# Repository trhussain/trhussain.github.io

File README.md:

npm run deploy 
- pushes to gh-pages dir

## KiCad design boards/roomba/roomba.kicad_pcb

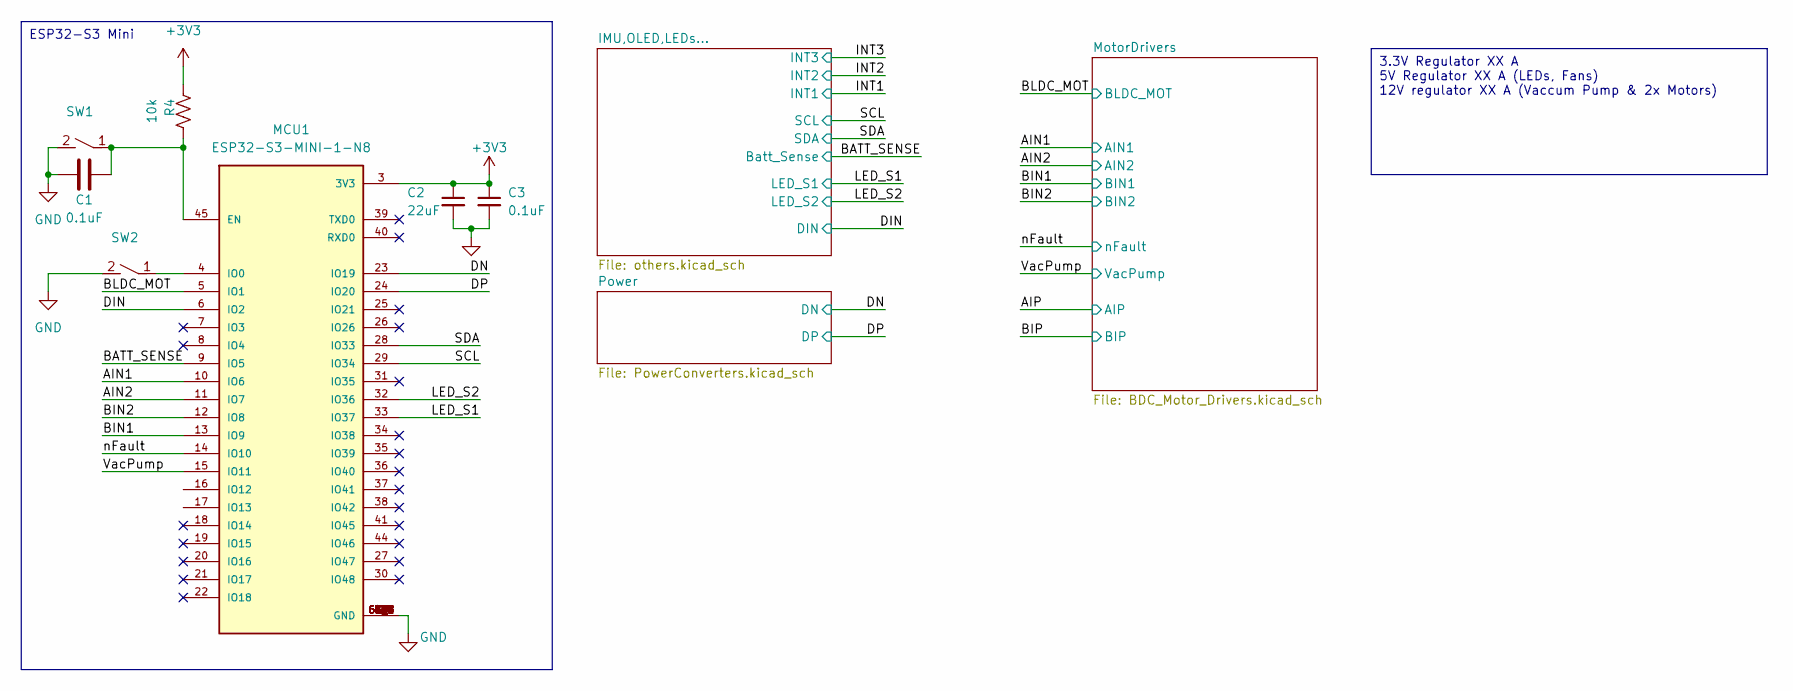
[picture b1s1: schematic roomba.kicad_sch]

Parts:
C1, C3: 0.1uF; C_0603_1608Metric
C2: 22uF; C_0603_1608Metric
MCU1: ESP32-S3-MINI-1-N8; XCVR_ESP32-S3-MINI-1-N8; PARTREV v0.6
R4: 10k; R_0603_1608Metric
SW1, SW2: rockerSwitch-434133025816

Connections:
+3V3: C2.1, C3.1, MCU1.3 (3V3), R4.2; also elsewhere on the board
/AIN1: MCU1.10 (IO6); also elsewhere on the board
/AIN2: MCU1.11 (IO7); also elsewhere on the board
/BATT_SENSE: MCU1.9 (IO5); also elsewhere on the board
/BIN1: MCU1.13 (IO9); also elsewhere on the board
/BIN2: MCU1.12 (IO8); also elsewhere on the board
/BLDC_MOT: MCU1.5 (IO1); also elsewhere on the board
/DIN: MCU1.6 (IO2); also elsewhere on the board
/DN: MCU1.23 (IO19); also elsewhere on the board
/DP: MCU1.24 (IO20); also elsewhere on the board
/LED_S1: MCU1.33 (IO37); also elsewhere on the board
/LED_S2: MCU1.32 (IO36); also elsewhere on the board
/SCL: MCU1.29 (IO34); also elsewhere on the board
/SDA: MCU1.28 (IO33); also elsewhere on the board
/VacPump: MCU1.15 (IO11); also elsewhere on the board
/nFault: MCU1.14 (IO10); also elsewhere on the board
GND: C1.1, C2.2, C3.2, MCU1.1 (GND), MCU1.2 (GND), MCU1.42 (GND), MCU1.43 (GND), MCU1.46 (GND), MCU1.47 (GND), MCU1.48 (GND), MCU1.49 (GND), MCU1.50 (GND), MCU1.51 (GND), MCU1.52 (GND), MCU1.53 (GND), MCU1.54 (GND), MCU1.55 (GND), MCU1.56 (GND), MCU1.57 (GND), MCU1.58 (GND), MCU1.59 (GND), MCU1.60 (GND), MCU1.61 (GND), MCU1.61_1 (GND), MCU1.61_2 (GND), MCU1.61_3 (GND), MCU1.61_4 (GND), MCU1.61_5 (GND), MCU1.61_6 (GND), MCU1.61_7 (GND), MCU1.61_8 (GND), MCU1.62 (GND), MCU1.63 (GND), MCU1.64 (GND), MCU1.65 (GND), SW1.2, SW2.2; also elsewhere on the board
unnamed: C1.2, MCU1.45 (EN), R4.1, SW1.1
unnamed: MCU1.4 (IO0), SW2.1

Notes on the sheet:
3.3V Regulator XX A 5V Regulator XX A (LEDs, Fans) 12V regulator XX A (Vaccum Pump & 2x Motors)
ESP32-S3 Mini

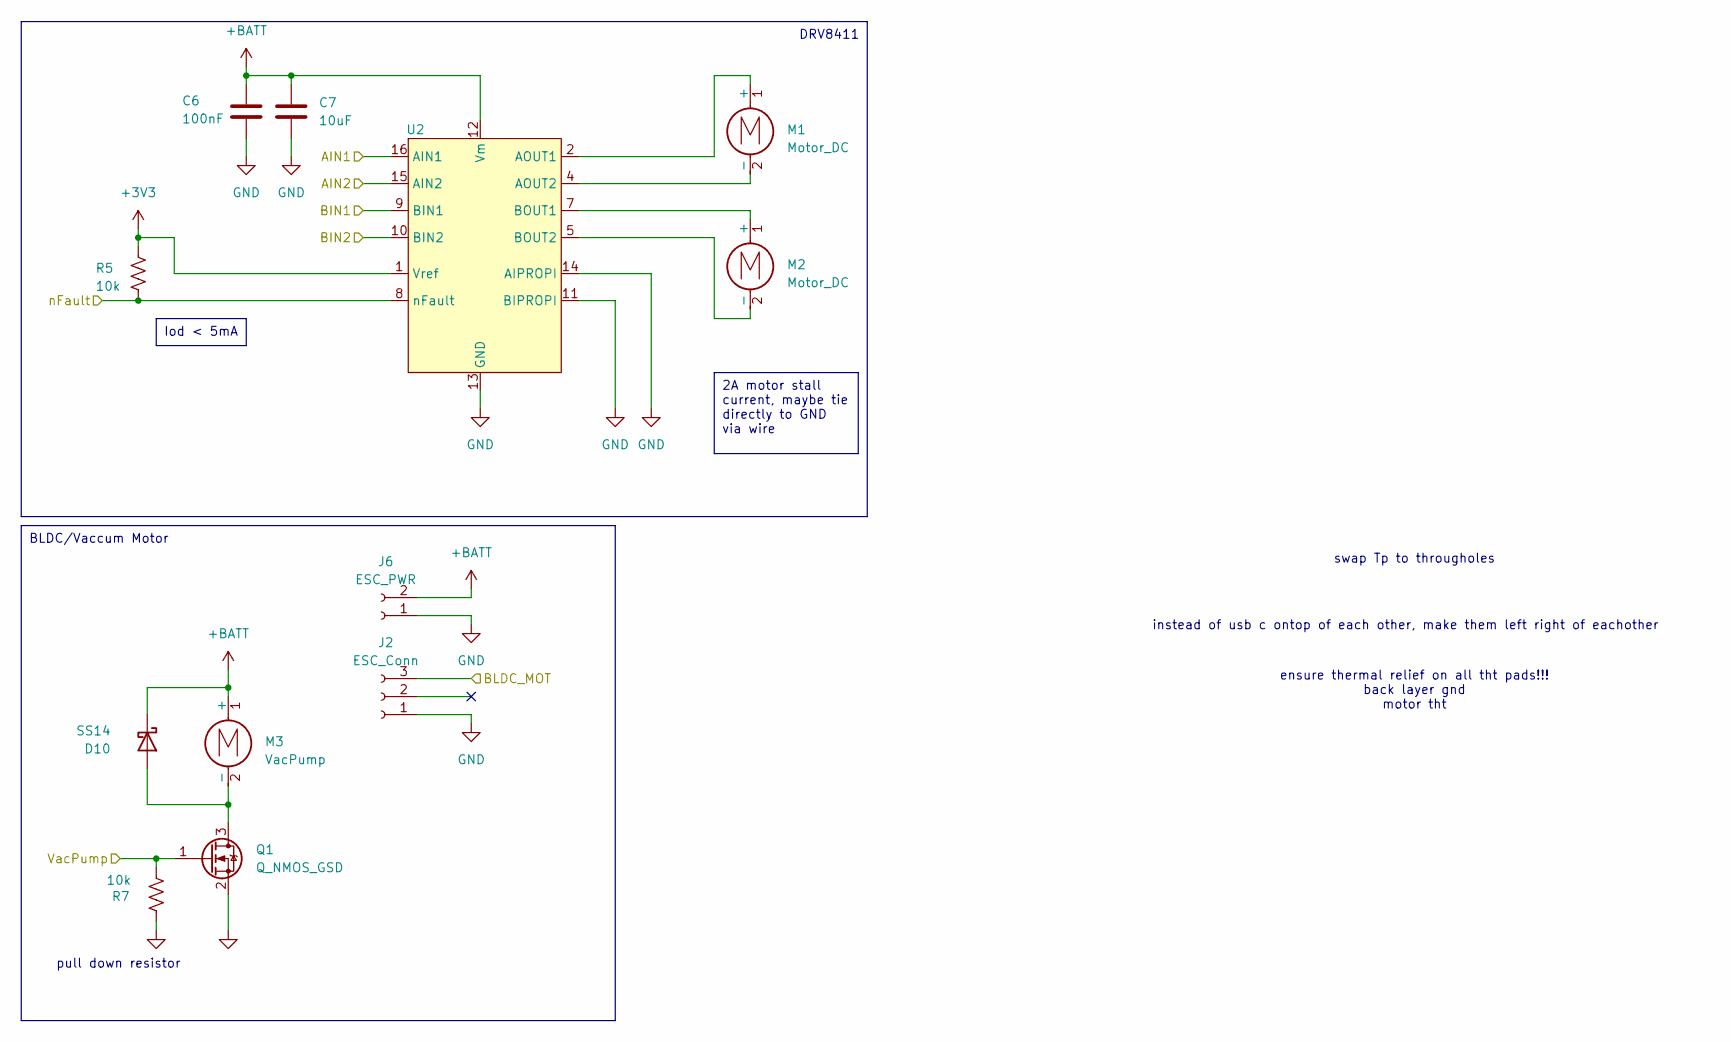
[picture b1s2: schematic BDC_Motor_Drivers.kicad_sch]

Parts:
C6: 100nF; C_0603_1608Metric_Pad1.08x0.95mm_HandSolder
C7: 10uF; C_0603_1608Metric_Pad1.08x0.95mm_HandSolder
D10: SS14; D_SMA
J2: ESC_Conn; PinHeader_1x03_P2.54mm_Horizontal
J6: ESC_PWR; PinSocket_1x02_P2.54mm_Vertical
M1, M2: Motor_DC; PinHeader_1x02_P2.54mm_Vertical
M3: VacPump; PinHeader_1x02_P2.54mm_Vertical
Q1: Q_NMOS_GSD; SOT-23-3
R5, R7: 10k; R_0603_1608Metric
U2: DRV8411A; TSSOP-DRV8411A

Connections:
+3V3: R5.1, U2.1 (Vref); also elsewhere on the board
+BATT: C6.1, C7.1, D10.1 (K), J6.2, M3.1 (+), U2.12 (Vm); also elsewhere on the board
/AIN1: U2.16 (AIN1); also elsewhere on the board
/AIN2: U2.15 (AIN2); also elsewhere on the board
/BIN1: U2.9 (BIN1); also elsewhere on the board
/BIN2: U2.10 (BIN2); also elsewhere on the board
/BLDC_MOT: J2.3; also elsewhere on the board
/VacPump: Q1.1 (G), R7.2; also elsewhere on the board
/nFault: R5.2, U2.8 (nFault); also elsewhere on the board
GND: C6.2, C7.2, J2.1, J6.1, Q1.2 (S), R7.1, U2.3 (PGNDA), U2.6 (PGNDB), U2.11 (BIPROPI), U2.13 (GND), U2.14 (AIPROPI), U2.19 (BODYGND); also elsewhere on the board
unnamed: D10.2 (A), M3.2 (-), Q1.3 (D)
unnamed: M1.1 (+), U2.2 (AOUT1)
unnamed: M1.2 (-), U2.4 (AOUT2)
unnamed: M2.1 (+), U2.7 (BOUT1)
unnamed: M2.2 (-), U2.5 (BOUT2)

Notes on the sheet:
Iod < 5mA
2A motor stall current, maybe tie directly to GND via wire
DRV8411
BLDC/Vaccum Motor
instead of usb c ontop of each other, make them left right of eachother
pull down resistor
ensure thermal relief on all tht pads!!! back layer gnd motor tht
swap Tp to througholes

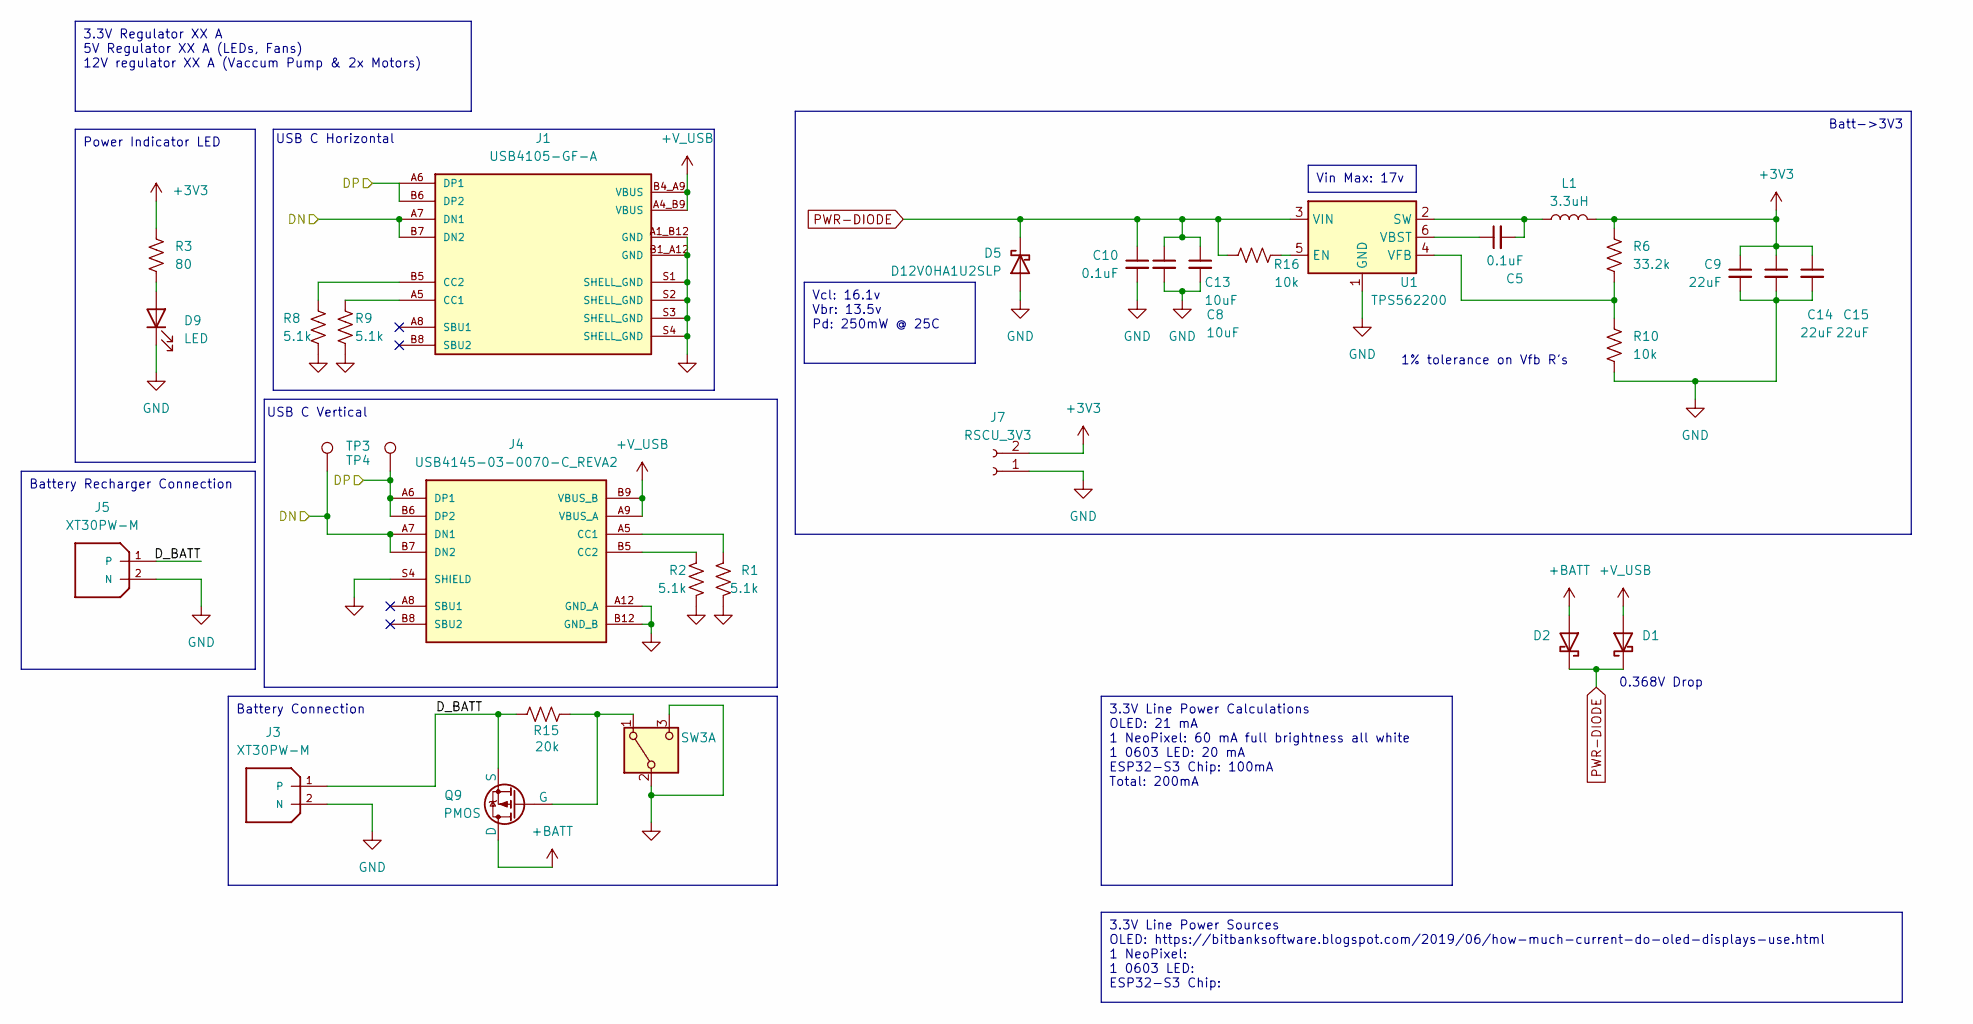
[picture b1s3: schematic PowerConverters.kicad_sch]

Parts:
C5, C10: 0.1uF; C_0603_1608Metric
C8, C13: 10uF; C_0603_1608Metric
C9, C14, C15: 22uF; C_0603_1608Metric
D1, D2: SS38; D_SOD-128
D5: D12V0HA1U2SLP; D_SOD-882
D9: LED; LED_0603_1608Metric
J1: USB4105-GF-A; GCT_USB4105-GF-A; PARTREV A3
J3: XT30PW-M; AMASS_XT30PW-M; PARTREV 1.2
J4: USB4145-03-0070-C_REVA2; GCT_USB4145-03-0070-C_REVA2; PARTREV A2
J5: XT30PW-M; AMASS_XT30U-F_1x02_P5.0mm_Vertical; PARTREV 1.2
J7: RSCU_3V3; PinSocket_1x02_P2.54mm_Vertical
L1: 3.3uH; L_TDK_VLS6045EX_VLS6045AF
Q9: PMOS; PowerPAK_SO-8_Single
R1, R2, R8, R9: 5.1k; R_0603_1608Metric
R3: 80; R_0603_1608Metric
R6: 33.2k; R_0603_1608Metric
R10, R16: 10k; R_0603_1608Metric
R15: 20k; R_0603_1608Metric
SW3: SW_Nidec_CAS-120A1; SW_JS102011JAQN
TP3, TP4: TestPoint; TestPoint_Pad_1.0x1.0mm
U1: TPS562200; SOT-23-6

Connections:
+3V3: C9.1, C14.1, C15.1, J7.2, L1.2, R3.1, R6.1; also elsewhere on the board
+BATT: D2.2 (A), Q9.5 (D); also elsewhere on the board
+V_USB: D1.2 (A), J1.A4_B9 (VBUS), J1.B4_A9 (VBUS), J4.A4 (VBUS_A), J4.A9 (VBUS_A), J4.B4 (VBUS_B), J4.B9 (VBUS_B)
/DN: J1.A7 (DN1), J1.B7 (DN2), J4.A7 (DN1), J4.B7 (DN2), TP3.1; also elsewhere on the board
/DP: J1.A6 (DP1), J1.B6 (DP2), J4.A6 (DP1), J4.B6 (DP2), TP4.1; also elsewhere on the board
/Power/D_BATT: J3.1, J5.1, Q9.1 (S), Q9.2 (S), Q9.3 (S), R15.2
GND: C8.2, C9.2, C10.2, C13.2, C14.2, C15.2, D5.2 (A), D9.1 (K), J1.A1_B12 (GND), J1.B1_A12 (GND), J1.S1 (SHELL_GND), J1.S2 (SHELL_GND), J1.S3 (SHELL_GND), J1.S4 (SHELL_GND), J3.2 (N), J4.A1 (GND_A), J4.A12 (GND_A), J4.B1 (GND_B), J4.B12 (GND_B), J4.S1 (SHIELD), J4.S2 (SHIELD), J4.S3 (SHIELD), J4.S4 (SHIELD), J5.2 (N), J7.1, R1.2, R2.2, R8.2, R9.2, R10.2, SW3.2 (B), SW3.3 (C), U1.1 (GND); also elsewhere on the board
unnamed: D9.2 (A), R3.2
unnamed: J1.A5 (CC1), R9.1
unnamed: J1.B5 (CC2), R8.1
unnamed: J4.A5 (CC1), R1.1
unnamed: J4.B5 (CC2), R2.1
unnamed: Q9.4 (G), R15.1, SW3.1 (A)
unnamed: R16.2, U1.5 (EN)
unnamed: C5.2, L1.1, U1.2 (SW)
unnamed: C5.1, U1.6 (VBST)
unnamed: R6.2, R10.1, U1.4 (VFB)
PWR-DIODE: C8.1, C10.1, C13.1, D1.1 (K), D2.1 (K), D5.1 (K), R16.1, U1.3 (VIN)

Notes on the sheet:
Vcl: 16.1v Vbr: 13.5v Pd: 250mW @ 25C
3.3V Line Power Calculations OLED: 21 mA 1 NeoPixel: 60 mA full brightness all white 1 0603 LED: 20 mA ESP32-S3 Chip: 100mA Total: 200mA
Vin Max: 17v
Batt->3V3
Battery Connection
3.3V Line Power Sources OLED: https://bitbanksoftware.blogspot.com/2019/06/how-much-current-do-oled-displays-use.html 1 NeoPixel: 1 0603 LED: ESP32-S3 Chip:
Power Indicator LED
Battery Recharger Connection
3.3V Regulator XX A 5V Regulator XX A (LEDs, Fans) 12V regulator XX A (Vaccum Pump & 2x Motors)
0.368V Drop
1% tolerance on Vfb R's
USB C Horizontal
USB C Vertical

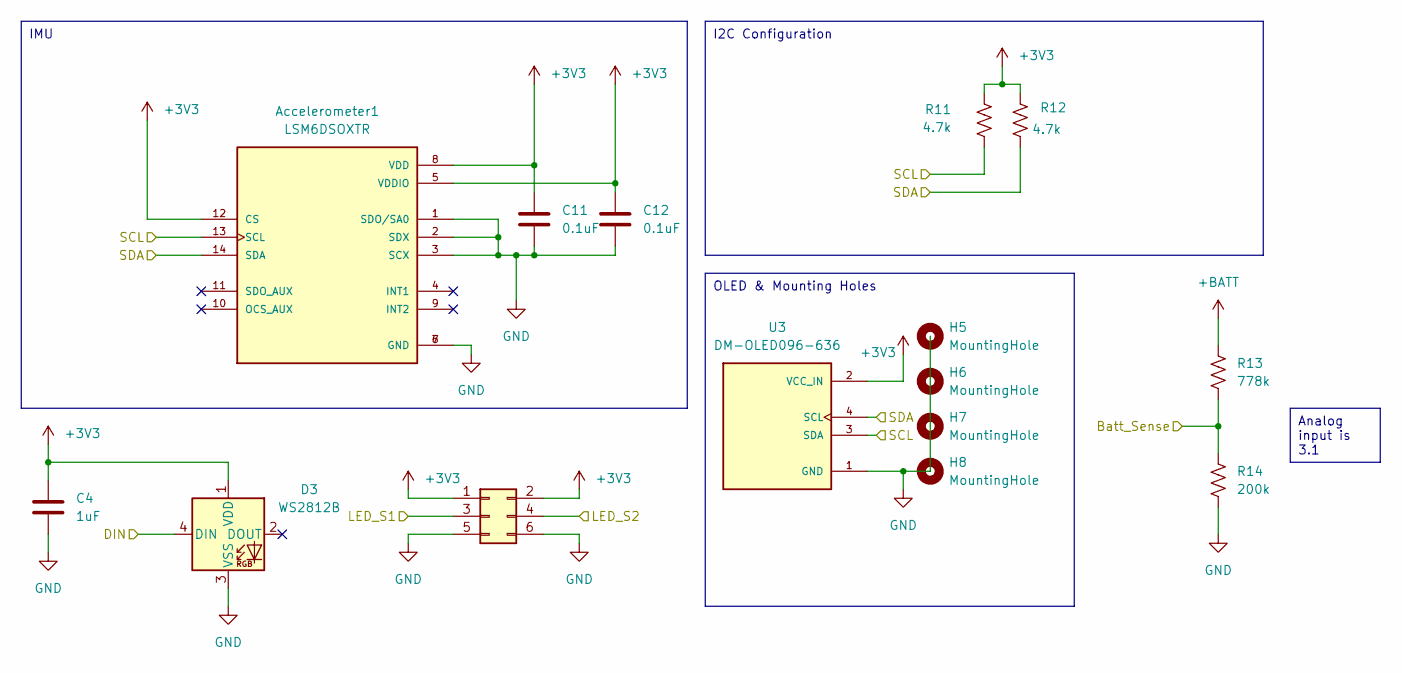
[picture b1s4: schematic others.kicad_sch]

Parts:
Accelerometer1: LSM6DSOXTR; PQFN50P250X300X86-14N; PARTREV 3.0
C4: 1uF; C_0603_1608Metric_Pad1.08x0.95mm_HandSolder
C11, C12: 0.1uF; C_0603_1608Metric
D3: WS2812B; LED_WS2812B_PLCC4_5.0x5.0mm_P3.2mm
H5, H6, H7, H8: MountingHole; MountingHole_2.2mm_M2
LED1: Conn_02x03_Odd_Even; PinHeader_2x03_P2.54mm_Horizontal
R11, R12: 4.7k; R_0603_1608Metric
R13: 778k; R_0603_1608Metric
R14: 200k; R_0603_1608Metric
U3: DM-OLED096-636; PinHeader_1x04_P2.54mm_Vertical; PARTREV 2018-09-10

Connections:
+3V3: Accelerometer1.5 (VDDIO), Accelerometer1.8 (VDD), Accelerometer1.12 (CS), C4.1, C11.1, C12.1, D3.1 (VDD), LED1.1, LED1.2, R11.2, R12.2, U3.2 (VCC_IN); also elsewhere on the board
+BATT: R13.1; also elsewhere on the board
/BATT_SENSE: R13.2, R14.1; also elsewhere on the board
/DIN: D3.4 (DIN); also elsewhere on the board
/LED_S1: LED1.3; also elsewhere on the board
/LED_S2: LED1.4; also elsewhere on the board
/SCL: Accelerometer1.13 (SCL), R11.1, U3.3 (SDA); also elsewhere on the board
/SDA: Accelerometer1.14 (SDA), R12.1, U3.4 (SCL); also elsewhere on the board
GND: Accelerometer1.1 (SDO/SA0), Accelerometer1.2 (SDX), Accelerometer1.3 (SCX), Accelerometer1.6 (GND), Accelerometer1.7 (GND), C4.2, C11.2, C12.2, D3.3 (VSS), LED1.5, LED1.6, R14.2, U3.1 (GND); also elsewhere on the board

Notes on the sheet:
I2C Configuration
Analog input is 3.1
OLED & Mounting Holes
IMU

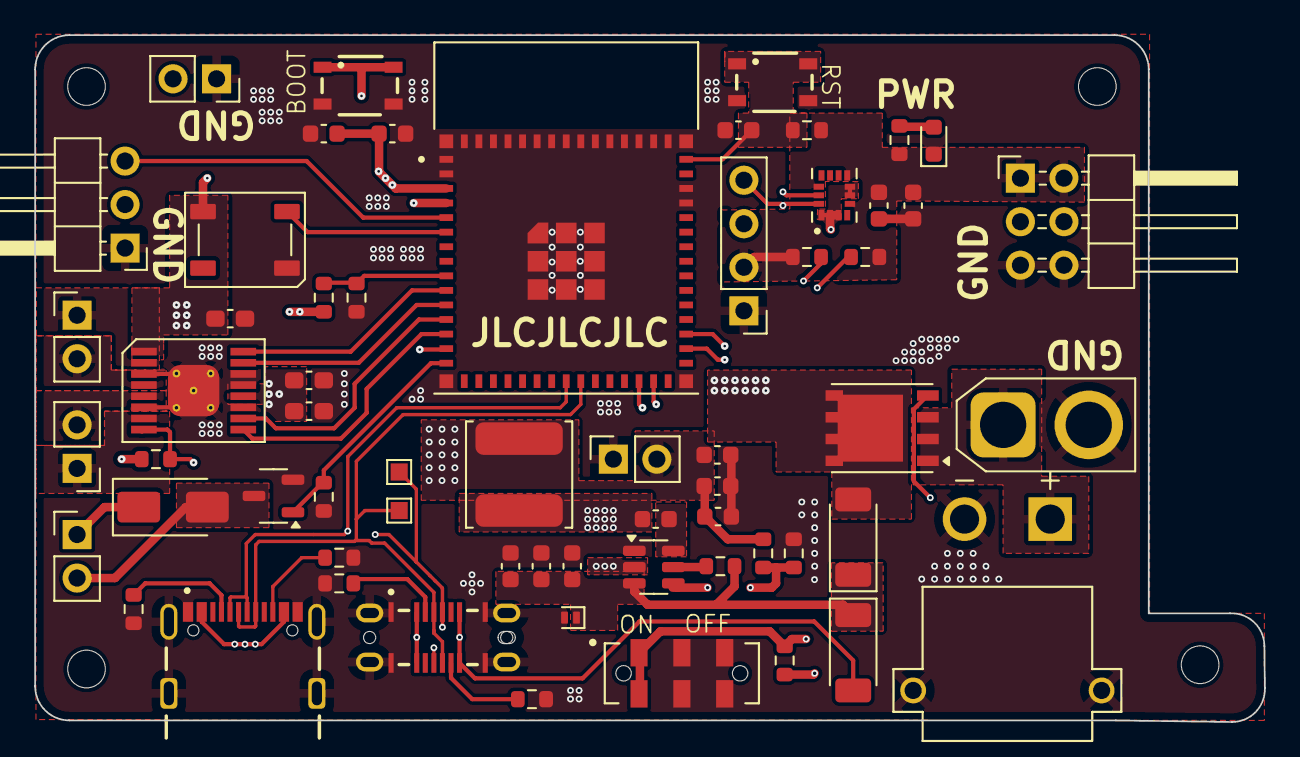
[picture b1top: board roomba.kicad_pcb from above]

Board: 4 copper layers, 71.8 x 40.1 mm, 65 parts (0 on the bottom side), 38 nets.

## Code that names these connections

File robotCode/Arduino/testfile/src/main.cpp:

#include <Arduino.h>
#include <FastLED.h>


#define LED_PIN 2
#define NUM_LEDS 1
#define AIN1 6
#define AIN2 7
#define BIN1 8
#define BIN2 9
CRGB led[NUM_LEDS];


void setup() {
 delay(1000);






 // Initialize the LED
 FastLED.addLeds<WS2812B, LED_PIN, GRB>(led, NUM_LEDS);
 FastLED.setBrightness(50); // Brightness level (0-255)
 led[0] = CRGB::Blue;
 FastLED.show();
 // USBSerial.begin(9600);
 pinMode(AIN1, OUTPUT);
 pinMode(AIN2, OUTPUT);
 pinMode(BIN1, OUTPUT);
 pinMode(BIN2, OUTPUT);
}


void loop() {

 Serial.println("test");
 delay(2000);
}

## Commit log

2024-10-27 Test
2024-10-27 Test V2
2024-10-27 header update
2024-10-27 Large pig push
2024-10-27 scripted commit call
2024-11-03 init commit, after deleting repo
2024-11-03 pushing back to new repo hope this works on god
2024-11-03 heyheyhey
2024-11-03 website v1 for submission
2024-11-04 hello
2024-11-05 karcher look at megit add . !
2024-11-07 use this guys
2025-01-05 Website Reset
2025-01-05 Repo reorganization & website transfer
2025-01-05 reorganization
2025-01-05 Model update
2025-01-13 pushing robot code
2025-01-13 temp save point
2025-01-13 saving before overrwriting with ESC test
2025-01-13 website update
2025-01-16 yay roller works
2025-01-20 final push for vroomba
2025-01-20 combot robot update
2025-01-24 video test
2026-05-02 update 2
2026-05-02 finished front page
2026-05-02 project list
2026-05-02 photo update
2026-05-03 honorable mentions
2026-05-03 sizing fix
2026-05-03 link update
2026-05-04 GA update
2026-05-18 new pi
2026-05-18 update reuse & microgrid
